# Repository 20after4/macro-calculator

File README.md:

# MacroCalculator

Custom Mechanical USB Keypad + Standalone Calculator written in MicroPython

## Hardware:

* Custom 24 Key Matrix PCB
    * Supports hot-swapable MX-style key switches
    * Hand solderable (Difficulty: medium-high due to small surface mount diodes)
    * Standard PC Numpad Keys
    * 7 extra macro keys
    * Sockets for MCU and LCD via pin headers.
* RPi Pico 2 (RP2350 MCU)
* 72x284 resolution ST7789 LCD Screen: 16px font = 4 lines x 17 characters

## Software / Firmware

Custom Python App running on [lvgl/lv_micropython](https://github.com/lvgl/lv_micropython) firmware.

The NumLock key toggles between two modes:

* Calc mode:
  * Basic calculator functionality
  * 17 digits of decimal precision
  * Basic expression evaluation
  * Named variables assignable to the macro keys
  * Scrollable history buffer
* Keypad mode:
  * Basic USB HID Numpad
  * Macro keys programmable with MicroPython for nearly unlimited flexibility.

### Acknoledgements

Here I credit the projects that made this one possible. This project draws on these other open source projects for inspiration and some of the components used in developing macro-calc:

* Raspberry Pi Pico - The RP2040 and successors have proven to be a very affordable and accessible microcontroller development platform which has significantly lowered the barrier to entry for embedded development.
* [MicroPython](https://www.micropython.org/): The programming language runtime and embedded firmware infrastructure.
* [LVGL](https://lvgl.io/) - Graphics API for embedded devices which I've utilized in order to support the LCD display in this project.
* [lvgl/lv_micropython](https://github.com/lvgl/lv_micropython) is a fork of micropython designed for building microcontroller Firmware with integrated LVGL graphics capabilities compiled into the micropython runtime. This is the foundation I've used to build the firmware for this project.
* [lvgl_micropython](https://github.com/lvgl-micropython/lvgl_micropython) deserves an honorable mention. This is an alternative fork, based on the previously mentioned project.  Although I don't currently use this fork to build my firmware, I have learned quite a lot about TFT Display chips from studying their source code, issues and discussions on github and on the lvgl forums.
* [mpy-dev/micropython-decimal-number](https://github.com/mpy-dev/micropython-decimal-number) provides
  a basis for sane decimal arithmatic. This has proven very helpful for the calculator portion of this project. Floating point math isn't a good fit for a general purpose calculator.

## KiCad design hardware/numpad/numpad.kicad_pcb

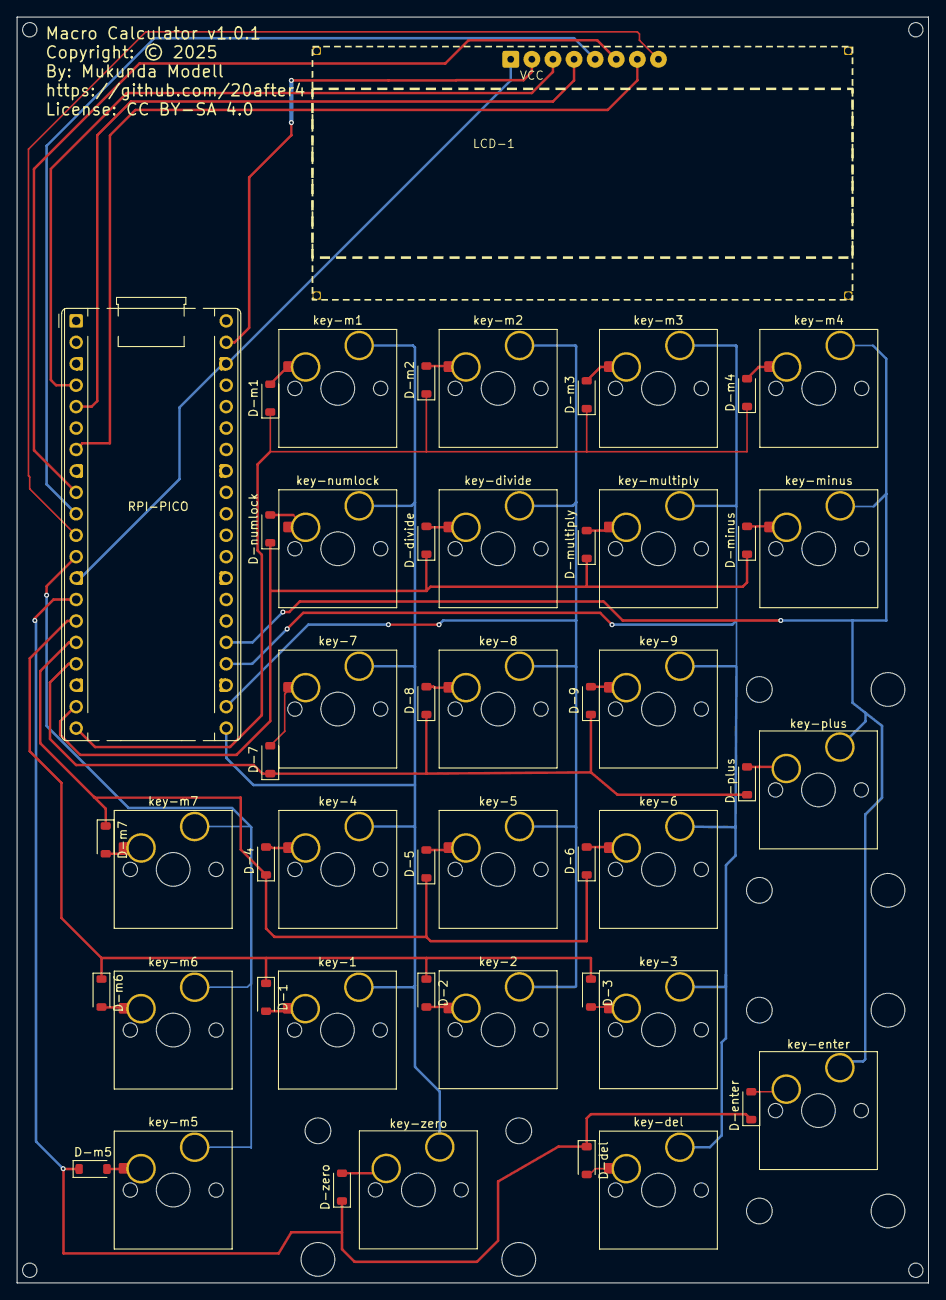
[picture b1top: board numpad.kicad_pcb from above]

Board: 2 copper layers, 108.0 x 150.0 mm, 50 parts (0 on the bottom side), 43 nets.

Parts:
D-1, D-2, D-3, D-4, D-5, D-6, D-7, D-8, D-9: D_SOD-123
D-del: D_SOD-123
D-divide: D_SOD-123
D-enter: D_SOD-123
D-m1, D-m2, D-m3, D-m4, D-m5, D-m6, D-m7: D_SOD-123
D-minus: D_SOD-123
D-multiply: D_SOD-123
D-numlock: D_SOD-123
D-plus: D_SOD-123
D-zero: D_SOD-123
LCD-1: 2.25in LCD; 2.25in LCD DISPLAY 284x76
RPI-PICO: RaspberryPi_Pico_Common_THT
key-1, key-2, key-3, key-4, key-5, key-6, key-7, key-8, key-9: SW_Cherry_MX_1.00u_PCB_HOTSWAP
key-del: SW_Cherry_MX_1.00u_PCB_HOTSWAP
key-divide: SW_Cherry_MX_1.00u_PCB_HOTSWAP
key-enter: SW_Cherry_MX_2.00u_Vertical_PCB
key-m1, key-m2, key-m3, key-m4, key-m5, key-m6, key-m7: SW_Cherry_MX_1.00u_PCB_HOTSWAP
key-minus: SW_Cherry_MX_1.00u_PCB_HOTSWAP
key-multiply: SW_Cherry_MX_1.00u_PCB_HOTSWAP
key-numlock: SW_Cherry_MX_1.00u_PCB_HOTSWAP
key-plus: SW_Cherry_MX_2.00u_Vertical_PCB
key-zero: SW_Cherry_MX_2.00u_PCB

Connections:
LCD-BACKLIGHT: LCD-1.8, RPI-PICO.11
LCD-CS: LCD-1.7 (BKLT), RPI-PICO.7
LCD-DC: LCD-1.6 (CS), RPI-PICO.9
LCD-RESET: LCD-1.5 (RES), RPI-PICO.10
unnamed: D-1.2 (A), key-1.2
unnamed: D-2.2 (A), key-2.2
unnamed: D-3.2 (A), key-3.2
unnamed: D-4.2 (A), key-4.2
unnamed: D-5.2 (A), key-5.2
unnamed: D-6.2 (A), key-6.2
unnamed: D-7.2 (A), key-7.2
unnamed: D-8.2 (A), key-8.2
unnamed: D-9.2 (A), key-9.2
unnamed: D-m1.2 (A), key-m1.2
unnamed: D-m2.2 (A), key-m2.2
unnamed: D-m3.2 (A), key-m3.2
unnamed: D-m4.2 (A), key-m4.2
unnamed: D-m5.2 (A), key-m5.2
unnamed: D-m6.2 (A), key-m6.2
unnamed: D-m7.2 (A), key-m7.2
SPI-CLK: LCD-1.3 (SCL), RPI-PICO.4
SPI-DATA: LCD-1.4 (SDA), RPI-PICO.5
col-0: RPI-PICO.12, key-m5.1, key-m6.1, key-m7.1
col-1: RPI-PICO.21, key-1.1, key-4.1, key-7.1, key-m1.1, key-numlock.1, key-zero.1
col-2: RPI-PICO.22, key-2.1, key-5.1, key-8.1, key-divide.1, key-m2.1
col-3: RPI-PICO.24, key-3.1, key-6.1, key-9.1, key-del.1, key-m3.1, key-multiply.1
col-4: RPI-PICO.25, key-enter.1, key-m4.1, key-minus.1, key-plus.1
gnd: LCD-1.1 (GND), RPI-PICO.13, RPI-PICO.38
key-del: D-del.2, key-del.2
key-divide: D-divide.2, key-divide.2
key-enter: D-enter.2, key-enter.2
key-minus: D-minus.2, key-minus.2
key-multiply: D-multiply.2, key-multiply.2
key-numlock: D-numlock.2, key-numlock.2
key-plus: D-plus.2, key-plus.2
key-zero: D-zero.2, key-zero.2
row-1: D-del.1, D-enter.1, D-m5.1 (K), D-zero.1, RPI-PICO.14
row-2: D-1.1 (K), D-2.1 (K), D-3.1 (K), D-m6.1 (K), RPI-PICO.15
row-3: D-4.1 (K), D-5.1 (K), D-6.1 (K), D-m7.1 (K), RPI-PICO.16
row-4: D-7.1 (K), D-8.1 (K), D-9.1 (K), D-plus.1, RPI-PICO.17
row-5: D-divide.1, D-minus.1, D-multiply.1, D-numlock.1, RPI-PICO.19
row-6: D-m1.1 (K), D-m2.1 (K), D-m3.1 (K), D-m4.1 (K), RPI-PICO.20
vcc: LCD-1.2 (VCC), RPI-PICO.39

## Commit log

2025-10-09 README.
2025-10-09 calc source
2025-10-09 PCB kicaed files
2025-10-09 GPL v3 & CC-BY-SA 4.0
2025-10-09 add pcb image
2025-10-09 thumbs + copyright notice
2025-10-10 Add Acknowledgements to readme and include some deps.
2025-10-19 Key class and better keyboard handling
2025-10-21 Better history management with a circular buffer
2025-10-21 Mostly added comments
2025-10-22 Code cleanup and comments

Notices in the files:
hardware/numpad/numpad.kicad_pcb:
Copyright: © 2025
License: CC BY-SA 4.0
